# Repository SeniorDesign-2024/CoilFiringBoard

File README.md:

# CoilFiringBoard
PCB design files for the Coil Firing Board

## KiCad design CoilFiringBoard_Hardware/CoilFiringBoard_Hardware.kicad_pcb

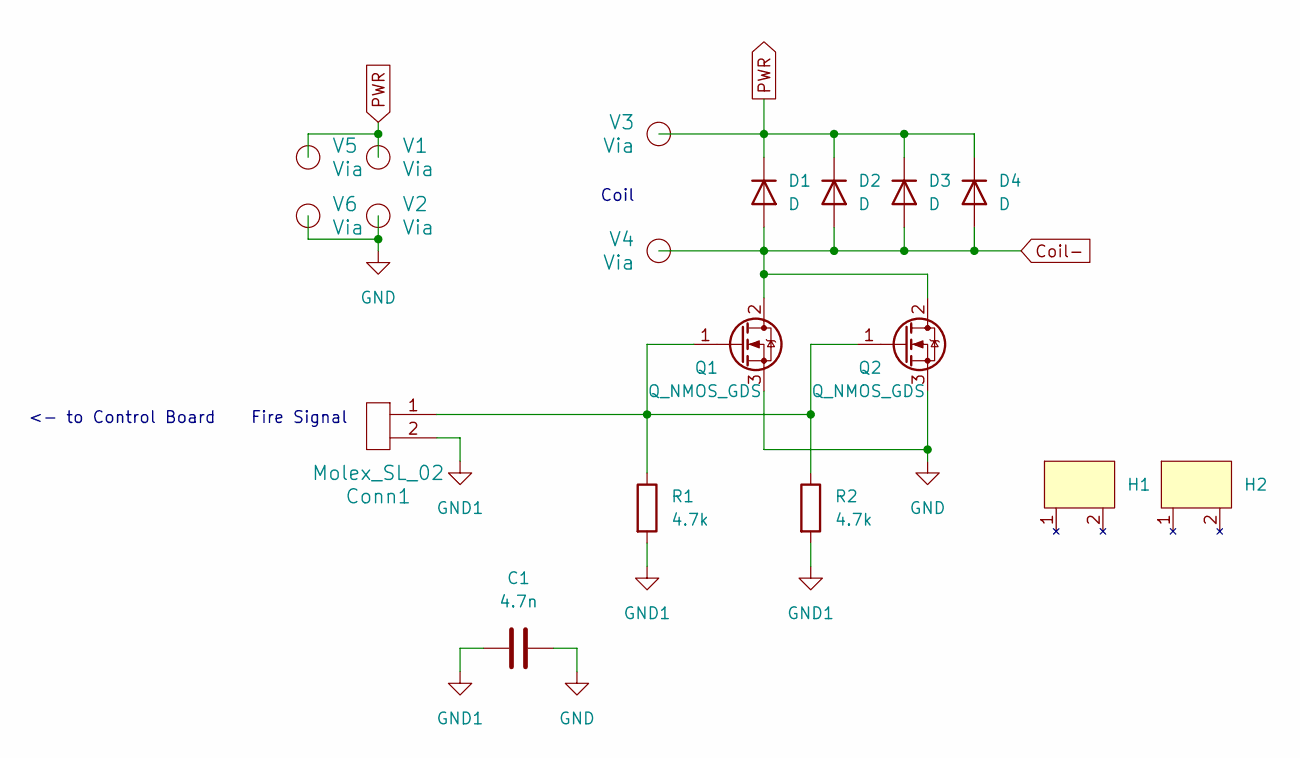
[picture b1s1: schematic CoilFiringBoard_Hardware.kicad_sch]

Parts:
C1: 4.7n; C_Rect_L13.0mm_W5.0mm_P10.00mm_FKS3_FKP3_MKS4
Conn1: Molex_SL_02; MOLEX_SL_02_Horizontal
D1, D2, D3, D4: D; D_DO-201AD_P12.70mm_Horizontal
H1, H2: WV-T264-101E
Q1, Q2: Q_NMOS_GDS; TO-264-3_Vertical
R1, R2: 4.7k; R_0603_1608Metric_Pad0.98x0.95mm_HandSolder
V1, V2, V5, V6: Via; BATT_PWR_VIA
V3, V4: Via; MountingHole_2.2mm_M2_DIN965_Pad

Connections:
Coil-: D1.2 (A), D2.2 (A), D3.2 (A), D4.2 (A), Q1.2 (D), Q2.2 (D), V4.1
GND: C1.2, Q1.3 (S), Q2.3 (S), V2.1, V6.1
GND1: C1.1, Conn1.2, R1.2, R2.2
unnamed: Conn1.1, Q1.1 (G), Q2.1 (G), R1.1, R2.1
PWR: D1.1 (K), D2.1 (K), D3.1 (K), D4.1 (K), V1.1, V3.1, V5.1

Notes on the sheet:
Coil
<- to Control Board Fire Signal

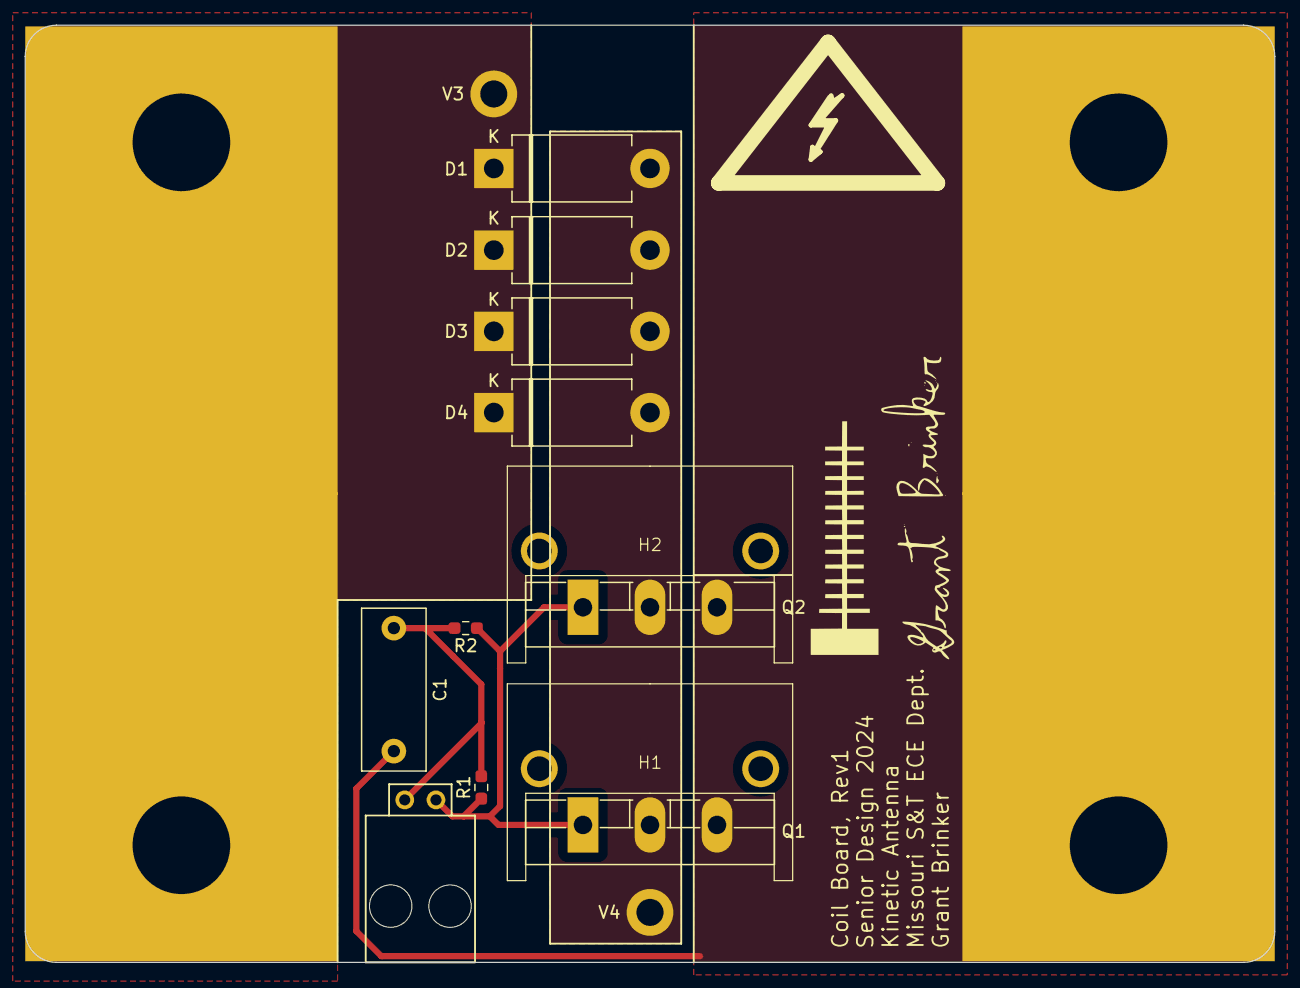
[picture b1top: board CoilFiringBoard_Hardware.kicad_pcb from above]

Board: 2 copper layers, 101.6 x 76.2 mm, 18 parts (0 on the bottom side), 5 nets.

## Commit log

2024-01-19 Made files
2024-01-24 Made schematic
2024-02-05 Changed FETs + added flyback diodes
2024-02-05 Made layout
2024-02-16 Updated layout
2024-02-19 Increased spacing + added Y cap
2024-02-19 Updated Coil- plane
2024-02-19 Adjusted pads and traces
2024-02-19 Adjusted gate traces
2024-02-21 Updated schematic
2024-02-22 Changed cap footprint
2024-02-22 Adjusted silkscreens
2024-02-22 Adjusted traces + silkscreens
2024-02-22 Fixed an error
2024-02-22 Updated datasheet link
2024-02-23 Made most review changes
2024-02-23 Heatsink footprint, STEP, and Gerbs
2024-02-23 Moved mounting holes + remade step and gerbs
2024-02-23 Made BOM
2024-02-27 zipped gerbs
2024-02-27 bom generated with prices
2024-02-27 links clickable
